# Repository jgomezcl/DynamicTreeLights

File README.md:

# Dynamic Tree Lights
Custom tree lights that react to changes in the environment lighting. Once a change is detected on an individual tree light it emits a white flash after a short delay followed by three more of random duration in random colors. These can also trigger nearby tree lights, so the flash propagates through the Christmas tree.

This project was inspired by CONSTELLACTION, an installation created by panGenerator for Copernicus Science Centre / Przemiany Festiwal 2013 (https://vimeo.com/76479685).

The PCBs are built around an Attiny84 microcontroller and require an ICSP to be programmed. I used an Arduino Nano with the sketch ArduinoISP.ino that can be found on the examples of the Arduino IDE.

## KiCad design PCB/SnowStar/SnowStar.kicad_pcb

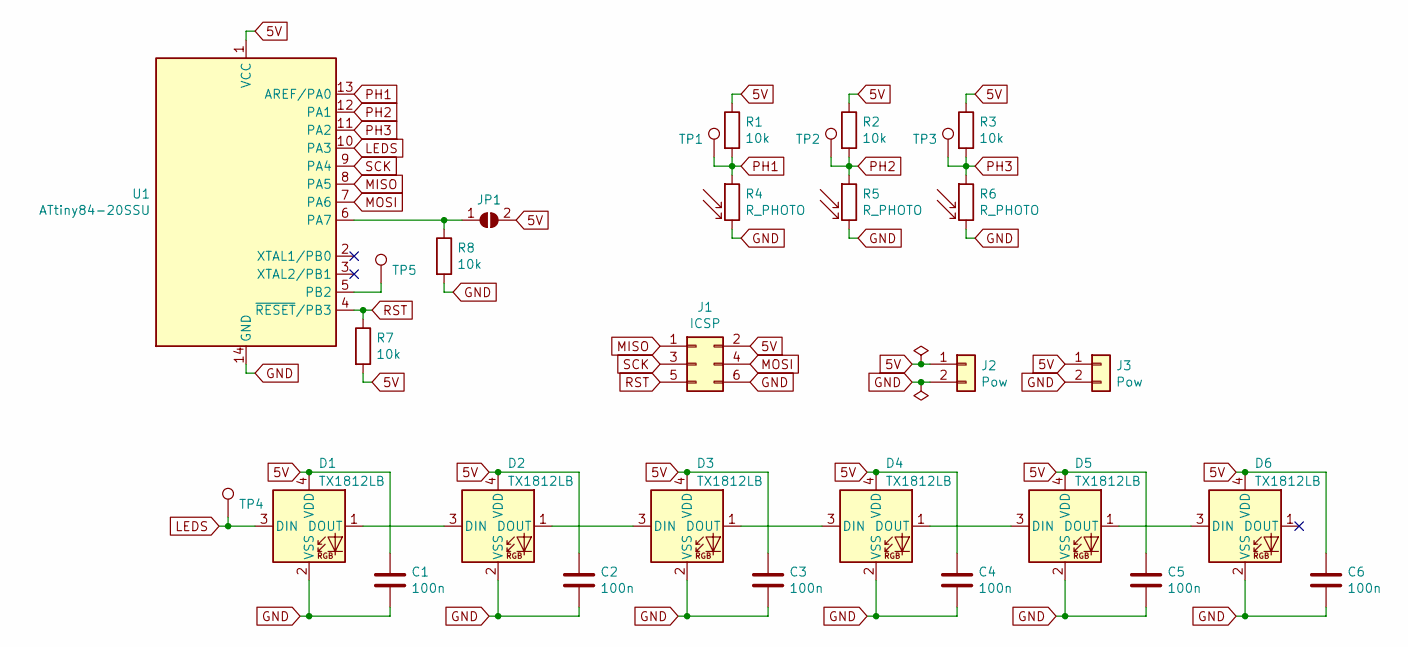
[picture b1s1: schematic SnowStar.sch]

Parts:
C1, C2, C3, C4, C5, C6: 100n; C_0603_1608Metric; LCSC Part # C14663
D1, D2, D3, D4, D5, D6: TX1812LB; LED_TX1812LB_TC2528RGB_2.4x2.7mm; LCSC Part # C784561
J1: ICSP; PinHeader_2x03_P2.54mm_Vertical
J2, J3: Pow; PinHeader_1x02_P2.54mm_Vertical
JP1: SolderJumper_2_Open; SolderJumper-2_P1.3mm_Open_Pad1.0x1.5mm
R1, R2, R3, R7, R8: 10k; R_0603_1608Metric; LCSC Part # C25804
R4, R5, R6: R_PHOTO; R_LDR_5.1x4.3mm_P3.4mm_Vertical
TP1, TP2, TP3, TP4, TP5: TestPoint; TestPoint_Pad_D1.5mm
U1: ATtiny84-20SSU; SOIC-14_3.9x8.7mm_P1.27mm

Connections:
5V: C1.1, C2.1, C3.1, C4.1, C5.1, C6.1, D1.4 (VDD), D2.4 (VDD), D3.4 (VDD), D4.4 (VDD), D5.4 (VDD), D6.4 (VDD), J1.2, J2.1, J3.1, JP1.2 (B), R1.1, R2.1, R3.1, R7.2, U1.1 (VCC)
GND: C1.2, C2.2, C3.2, C4.2, C5.2, C6.2, D1.2 (VSS), D2.2 (VSS), D3.2 (VSS), D4.2 (VSS), D5.2 (VSS), D6.2 (VSS), J1.6, J2.2, J3.2, R4.2, R5.2, R6.2, R8.2, U1.14 (GND)
LEDS: D1.3 (DIN), TP4.1, U1.10 (PA3)
MISO: J1.1, U1.8 (PA5)
MOSI: J1.4, U1.7 (PA6)
unnamed: D1.1 (DOUT), D2.3 (DIN)
unnamed: D2.1 (DOUT), D3.3 (DIN)
unnamed: D3.1 (DOUT), D4.3 (DIN)
unnamed: D4.1 (DOUT), D5.3 (DIN)
unnamed: D5.1 (DOUT), D6.3 (DIN)
unnamed: JP1.1 (A), R8.1, U1.6 (PA7)
unnamed: TP5.1, U1.5 (PB2)
PH1: R1.2, R4.1, TP1.1, U1.13 (AREF/PA0)
PH2: R2.2, R5.1, TP2.1, U1.12 (PA1)
PH3: R3.2, R6.1, TP3.1, U1.11 (PA2)
RST: J1.5, R7.1, U1.4 (~RESET~/PB3)
SCK: J1.3, U1.9 (PA4)

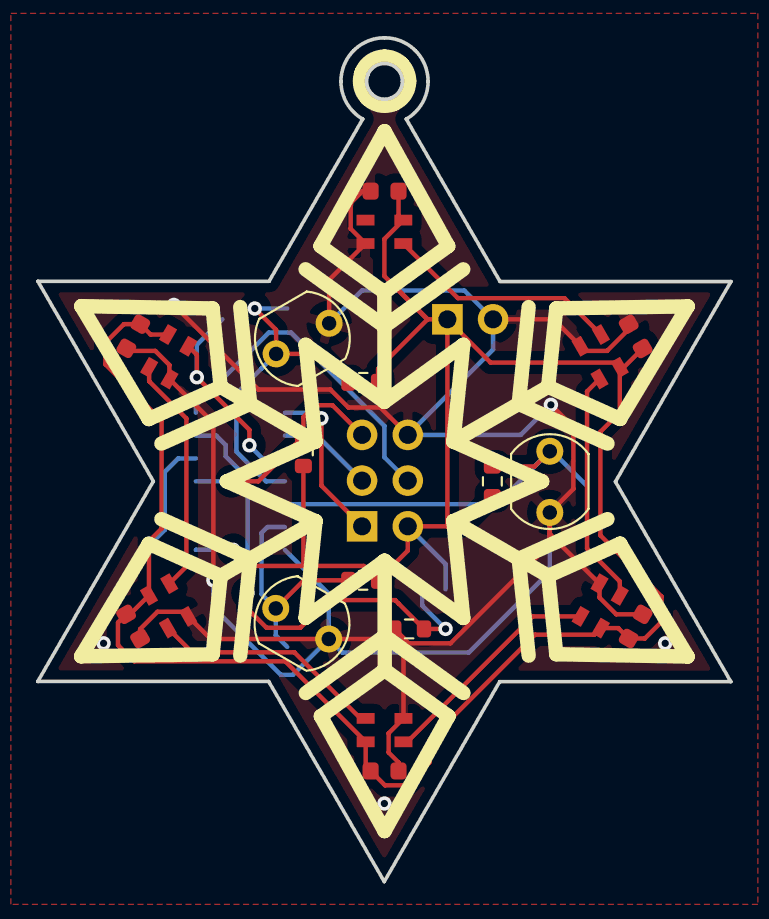
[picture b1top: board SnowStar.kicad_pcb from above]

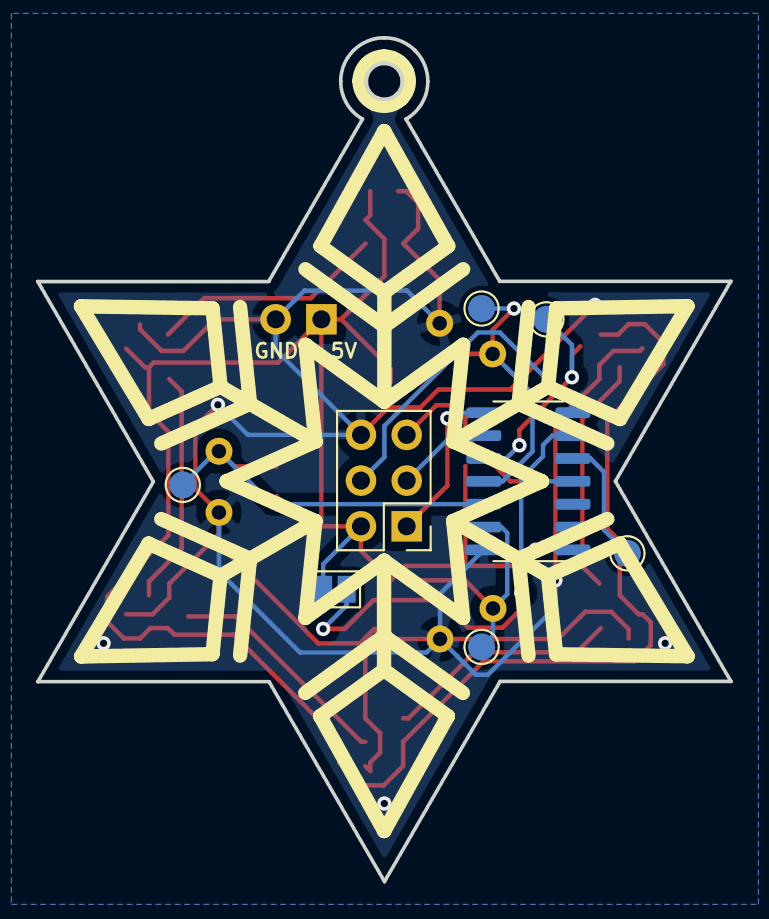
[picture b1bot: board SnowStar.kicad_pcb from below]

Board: 2 copper layers, 38.5 x 46.9 mm, 29 parts (8 on the bottom side), 17 nets.

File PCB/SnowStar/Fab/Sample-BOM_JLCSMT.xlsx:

Comment | Designator | Footprint | JLCPCB Part #（optional）
100n | C1 | Capacitor_SMD:C_0603_1608Metric | C14663
100n | C2 | Capacitor_SMD:C_0603_1608Metric | C14663
100n | C3 | Capacitor_SMD:C_0603_1608Metric | C14663
100n | C4 | Capacitor_SMD:C_0603_1608Metric | C14663
100n | C5 | Capacitor_SMD:C_0603_1608Metric | C14663
100n | C6 | Capacitor_SMD:C_0603_1608Metric | C14663
TX1812LB | D1 | SnowStar:LED_TX1812LB_TC2528RGB_2,4x2,7mm | C784561
TX1812LB | D2 | SnowStar:LED_TX1812LB_TC2528RGB_2,4x2,7mm | C784561
TX1812LB | D3 | SnowStar:LED_TX1812LB_TC2528RGB_2,4x2,7mm | C784561
TX1812LB | D4 | SnowStar:LED_TX1812LB_TC2528RGB_2,4x2,7mm | C784561
TX1812LB | D5 | SnowStar:LED_TX1812LB_TC2528RGB_2,4x2,7mm | C784561
TX1812LB | D6 | SnowStar:LED_TX1812LB_TC2528RGB_2,4x2,7mm | C784561
ICSP | J1 | Connector_PinHeader_2,54mm:PinHeader_2x03_P2,54mm_Vertical
Pow | J2 | Connector_PinHeader_2,54mm:PinHeader_1x02_P2,54mm_Vertical
Pow | J3 | Connector_PinHeader_2,54mm:PinHeader_1x02_P2,54mm_Vertical
SolderJumper_2_Open | JP1 | Jumper:SolderJumper-2_P1,3mm_Open_Pad1,0x1,5mm
10k | R1 | Resistor_SMD:R_0603_1608Metric | C25804
10k | R2 | Resistor_SMD:R_0603_1608Metric | C25804
10k | R3 | Resistor_SMD:R_0603_1608Metric | C25804
R_PHOTO | R4 | OptoDevice:R_LDR_5,1x4,3mm_P3,4mm_Vertical
R_PHOTO | R5 | OptoDevice:R_LDR_5,1x4,3mm_P3,4mm_Vertical
R_PHOTO | R6 | OptoDevice:R_LDR_5,1x4,3mm_P3,4mm_Vertical
10k | R7 | Resistor_SMD:R_0603_1608Metric | C25804
10k | R8 | Resistor_SMD:R_0603_1608Metric | C25804
ATtiny84-20SSU | U1 | Package_SO:SOIC-14_3,9x8,7mm_P1,27mm

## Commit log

2021-12-04 First update
2021-12-07 Added spontaneous blink feature
